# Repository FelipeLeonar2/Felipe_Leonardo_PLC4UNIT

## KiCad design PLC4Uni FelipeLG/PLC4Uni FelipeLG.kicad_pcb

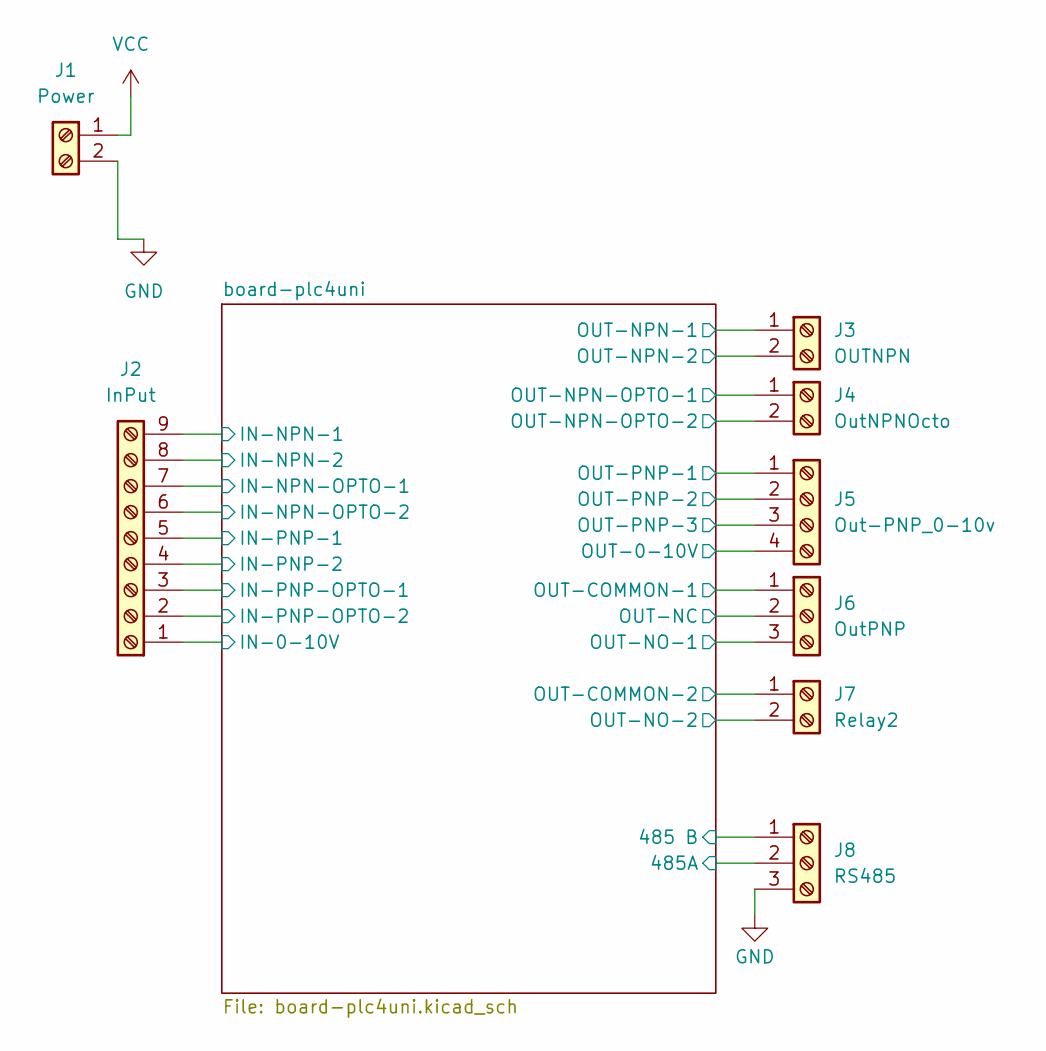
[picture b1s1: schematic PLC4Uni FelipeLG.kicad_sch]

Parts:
J1: Power; TerminalBlock_Phoenix_PT-1,5-2-5.0-H_1x02_P5.00mm_Horizontal
J2: InPut; TerminalBlock_Phoenix_PT-1,5-9-5.0-H_1x09_P5.00mm_Horizontal
J3: OUTNPN; TerminalBlock_Phoenix_PT-1,5-2-5.0-H_1x02_P5.00mm_Horizontal
J4: OutNPNOcto; TerminalBlock_Phoenix_PT-1,5-2-5.0-H_1x02_P5.00mm_Horizontal
J5: Out-PNP_0-10v; TerminalBlock_Phoenix_PT-1,5-4-5.0-H_1x04_P5.00mm_Horizontal
J6: OutPNP; TerminalBlock_Phoenix_PT-1,5-3-5.0-H_1x03_P5.00mm_Horizontal
J7: Relay2; TerminalBlock_Phoenix_PT-1,5-2-5.0-H_1x02_P5.00mm_Horizontal
J8: RS485; TerminalBlock_Phoenix_PT-1,5-3-5.0-H_1x03_P5.00mm_Horizontal

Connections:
/board-plc4uni/485 B: J8.1; also elsewhere on the board
/board-plc4uni/485A: J8.2; also elsewhere on the board
/board-plc4uni/IN-0-10V: J2.1; also elsewhere on the board
/board-plc4uni/IN-NPN-1: J2.9; also elsewhere on the board
/board-plc4uni/IN-NPN-2: J2.8; also elsewhere on the board
/board-plc4uni/IN-NPN-OPTO-1: J2.7; also elsewhere on the board
/board-plc4uni/IN-NPN-OPTO-2: J2.6; also elsewhere on the board
/board-plc4uni/IN-PNP-1: J2.5; also elsewhere on the board
/board-plc4uni/IN-PNP-2: J2.4; also elsewhere on the board
/board-plc4uni/IN-PNP-OPTO-1: J2.3; also elsewhere on the board
/board-plc4uni/IN-PNP-OPTO-2: J2.2; also elsewhere on the board
/board-plc4uni/OUT-0-10V: J5.4; also elsewhere on the board
/board-plc4uni/OUT-COMMON-1: J6.1; also elsewhere on the board
/board-plc4uni/OUT-COMMON-2: J7.1; also elsewhere on the board
/board-plc4uni/OUT-NC: J6.2; also elsewhere on the board
/board-plc4uni/OUT-NO-1: J6.3; also elsewhere on the board
/board-plc4uni/OUT-NO-2: J7.2; also elsewhere on the board
/board-plc4uni/OUT-NPN-1: J3.1; also elsewhere on the board
/board-plc4uni/OUT-NPN-2: J3.2; also elsewhere on the board
/board-plc4uni/OUT-NPN-OPTO-1: J4.1; also elsewhere on the board
/board-plc4uni/OUT-NPN-OPTO-2: J4.2; also elsewhere on the board
/board-plc4uni/OUT-PNP-1: J5.1; also elsewhere on the board
/board-plc4uni/OUT-PNP-2: J5.2; also elsewhere on the board
/board-plc4uni/OUT-PNP-3: J5.3; also elsewhere on the board
GND: J1.2, J8.3; also elsewhere on the board
VCC: J1.1; also elsewhere on the board

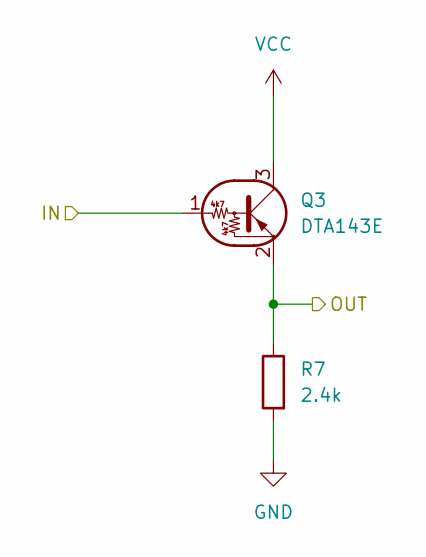
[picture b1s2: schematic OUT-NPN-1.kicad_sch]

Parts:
Q3: DTA143E; SC-59
R7: 2.4k; R_0603_1608Metric

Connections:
/board-plc4uni/OUT-NPN-2: Q3.2 (E), R7.2; also elsewhere on the board
/board-plc4uni/OUT-NPN-2/IN: Q3.1 (B); also elsewhere on the board
GND: R7.1; also elsewhere on the board
VCC: Q3.3 (C); also elsewhere on the board

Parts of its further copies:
Q7: DTA143E; SC-59
R21: 2.4k; R_0603_1608Metric

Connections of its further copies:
/board-plc4uni/OUT-NPN-1: Q7.2 (E), R21.2; also elsewhere on the board
/board-plc4uni/OUT-NPN-1/IN: Q7.1 (B); also elsewhere on the board
GND: R21.1; also elsewhere on the board
VCC: Q7.3 (C); also elsewhere on the board

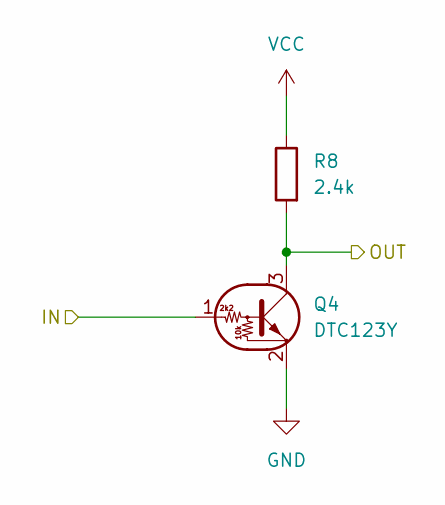
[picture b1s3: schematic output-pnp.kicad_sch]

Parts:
Q4: DTC123Y; SOT-23
R8: 2.4k; R_0603_1608Metric

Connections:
/board-plc4uni/OUT-PNP-1: Q4.3 (C), R8.1; also elsewhere on the board
/board-plc4uni/output-pnp-1/IN: Q4.1 (B); also elsewhere on the board
GND: Q4.2 (E); also elsewhere on the board
VCC: R8.2; also elsewhere on the board

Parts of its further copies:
Q8, Q9: DTC123Y; SOT-23
R22, R23: 2.4k; R_0603_1608Metric

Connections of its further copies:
/board-plc4uni/OUT-PNP-2: Q8.3 (C), R22.1; also elsewhere on the board
/board-plc4uni/OUT-PNP-3: Q9.3 (C), R23.1; also elsewhere on the board
/board-plc4uni/output-pnp-2/IN: Q8.1 (B); also elsewhere on the board
/board-plc4uni/output-pnp-3/IN: Q9.1 (B); also elsewhere on the board
GND: Q8.2 (E), Q9.2 (E); also elsewhere on the board
VCC: R22.2, R23.2; also elsewhere on the board

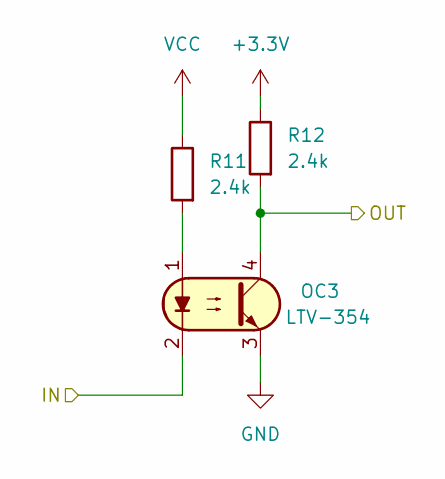
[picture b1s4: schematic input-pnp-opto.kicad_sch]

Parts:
OC3: FOD817S; SMDIP-4_W9.53mm; Part Number LTV-354
R11, R12: 2.4k; R_0603_1608Metric

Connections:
+3.3V: R12.2; also elsewhere on the board
/board-plc4uni/IN-PNP-OPTO-1: OC3.2; also elsewhere on the board
/board-plc4uni/input-pnp-opto-1/OUT: OC3.4, R12.1; also elsewhere on the board
GND: OC3.3; also elsewhere on the board
unnamed: OC3.1, R11.1
VCC: R11.2; also elsewhere on the board

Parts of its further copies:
OC5: FOD817S; SMDIP-4_W9.53mm; Part Number LTV-354
R16, R17: 2.4k; R_0603_1608Metric

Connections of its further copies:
+3.3V: R17.2; also elsewhere on the board
/board-plc4uni/IN-PNP-OPTO-2: OC5.2; also elsewhere on the board
/board-plc4uni/input-pnp-opto-2/OUT: OC5.4, R17.1; also elsewhere on the board
GND: OC5.3; also elsewhere on the board
unnamed: OC5.1, R16.1
VCC: R16.2; also elsewhere on the board

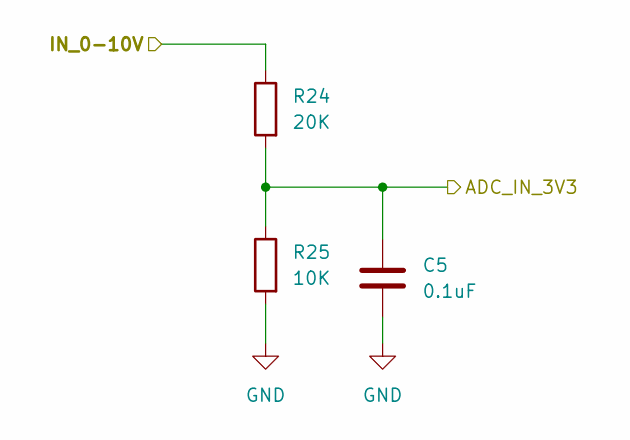
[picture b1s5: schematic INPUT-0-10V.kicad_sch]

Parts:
C5: 0.1uF; C_0201_0603Metric; LCSC C66501
R24: 20K; R_0603_1608Metric
R25: 10K; R_0603_1608Metric

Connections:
/board-plc4uni/IN-0-10V: R24.2; also elsewhere on the board
/board-plc4uni/INPUT-0-10V/ADC_IN_3V3: C5.2, R24.1, R25.2; also elsewhere on the board
GND: C5.1, R25.1; also elsewhere on the board

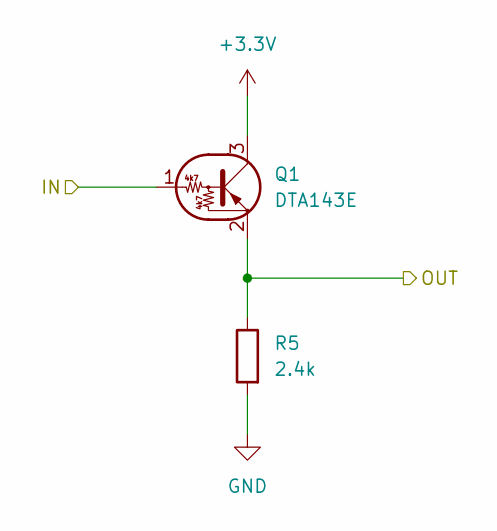
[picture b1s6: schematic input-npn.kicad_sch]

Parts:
Q1: DTA143E; SC-59
R5: 2.4k; R_0603_1608Metric

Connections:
+3.3V: Q1.3 (C); also elsewhere on the board
/board-plc4uni/IN-NPN-1: Q1.1 (B); also elsewhere on the board
/board-plc4uni/input-npn-1/OUT: Q1.2 (E), R5.2; also elsewhere on the board
GND: R5.1; also elsewhere on the board

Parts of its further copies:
Q5: DTA143E; SC-59
R15: 2.4k; R_0603_1608Metric

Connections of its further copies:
+3.3V: Q5.3 (C); also elsewhere on the board
/board-plc4uni/IN-NPN-2: Q5.1 (B); also elsewhere on the board
/board-plc4uni/input-npn-2/OUT: Q5.2 (E), R15.2; also elsewhere on the board
GND: R15.1; also elsewhere on the board

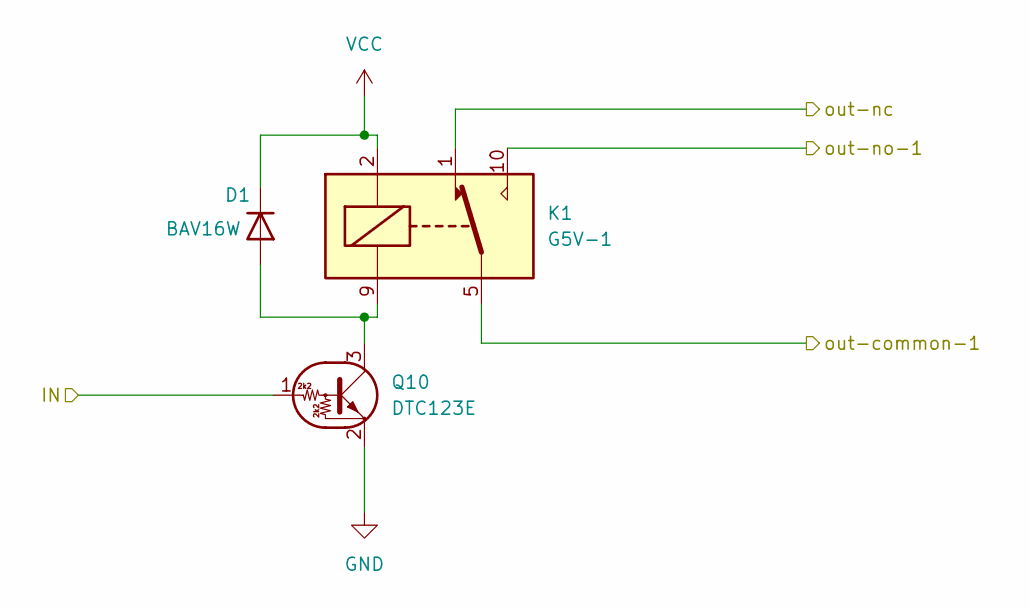
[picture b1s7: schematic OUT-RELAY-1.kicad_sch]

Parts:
D1: 1N4148WT; D_SOD-523; Part number BAV16W
K1: G5V-1; Relay_SPDT_Omron_G5V-1
Q10: DTC123E; SOT-23

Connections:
/board-plc4uni/OUT-COMMON-1: K1.5, K1.6; also elsewhere on the board
/board-plc4uni/OUT-NC: K1.1; also elsewhere on the board
/board-plc4uni/OUT-NO-1: K1.10; also elsewhere on the board
/board-plc4uni/OUT-RELAY-1/IN: Q10.1 (B); also elsewhere on the board
GND: Q10.2 (E); also elsewhere on the board
unnamed: D1.2 (A), K1.9, Q10.3 (C)
VCC: D1.1 (K), K1.2; also elsewhere on the board

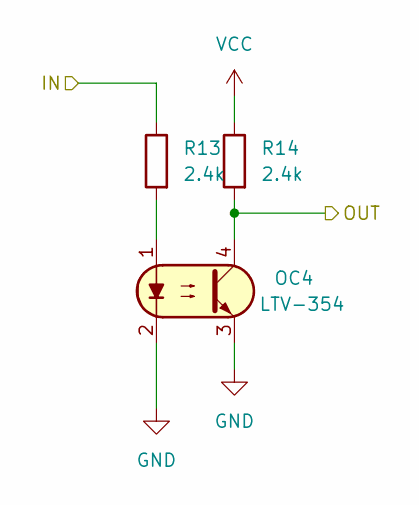
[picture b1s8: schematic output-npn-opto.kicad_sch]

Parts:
OC4: FOD817S; SMDIP-4_W9.53mm; Part Number LTV-354
R13, R14: 2.4k; R_0603_1608Metric

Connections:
/board-plc4uni/OUT-NPN-OPTO-1: OC4.4, R14.1; also elsewhere on the board
/board-plc4uni/output-npn-opto-1/IN: R13.2; also elsewhere on the board
GND: OC4.2, OC4.3; also elsewhere on the board
unnamed: OC4.1, R13.1
VCC: R14.2; also elsewhere on the board

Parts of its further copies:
OC6: FOD817S; SMDIP-4_W9.53mm; Part Number LTV-354
R19, R20: 2.4k; R_0603_1608Metric

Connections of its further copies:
/board-plc4uni/OUT-NPN-OPTO-2: OC6.4, R20.1; also elsewhere on the board
/board-plc4uni/output-npn-opto-2/IN: R19.2; also elsewhere on the board
GND: OC6.2, OC6.3; also elsewhere on the board
unnamed: OC6.1, R19.1
VCC: R20.2; also elsewhere on the board

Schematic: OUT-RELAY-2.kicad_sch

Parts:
D3: 1N4148WT; D_SOD-523; Part number BAV16W
K2: G5V-1; Relay_SPDT_Omron_G5V-1
Q11: DTC123E; SOT-23

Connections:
/board-plc4uni/OUT-COMMON-2: K2.5, K2.6; also elsewhere on the board
/board-plc4uni/OUT-NO-2: K2.10; also elsewhere on the board
/board-plc4uni/OUT-RELAY-2/IN: Q11.1 (B); also elsewhere on the board
GND: Q11.2 (E); also elsewhere on the board
unnamed: D3.2 (A), K2.9, Q11.3 (C)
VCC: D3.1 (K), K2.2; also elsewhere on the board

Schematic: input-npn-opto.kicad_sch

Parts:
OC1: FOD817S; SMDIP-4_W9.53mm; Part Number LTV-354
R3, R4: 2.4k; R_0603_1608Metric

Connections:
+3.3V: R4.2; also elsewhere on the board
/board-plc4uni/IN-NPN-OPTO-2: R3.1; also elsewhere on the board
/board-plc4uni/input-npn-opto-2/OUT: OC1.4, R4.1; also elsewhere on the board
GND: OC1.2, OC1.3; also elsewhere on the board
unnamed: OC1.1, R3.2

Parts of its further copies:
OC2: FOD817S; SMDIP-4_W9.53mm; Part Number LTV-354
R9, R10: 2.4k; R_0603_1608Metric

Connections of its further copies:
+3.3V: R10.2; also elsewhere on the board
/board-plc4uni/IN-NPN-OPTO-1: R9.1; also elsewhere on the board
/board-plc4uni/input-npn-opto-1/OUT: OC2.4, R10.1; also elsewhere on the board
GND: OC2.2, OC2.3; also elsewhere on the board
unnamed: OC2.1, R9.2

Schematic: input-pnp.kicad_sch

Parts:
Q2: DTC123E; SOT-23
R6: 2.4k; R_0603_1608Metric

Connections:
+3.3V: R6.2; also elsewhere on the board
/board-plc4uni/IN-PNP-1: Q2.1 (B); also elsewhere on the board
/board-plc4uni/input-pnp-1/OUT: Q2.3 (C), R6.1; also elsewhere on the board
GND: Q2.2 (E); also elsewhere on the board

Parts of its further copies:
Q6: DTC123E; SOT-23
R18: 2.4k; R_0603_1608Metric

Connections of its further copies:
+3.3V: R18.2; also elsewhere on the board
/board-plc4uni/IN-PNP-2: Q6.1 (B); also elsewhere on the board
/board-plc4uni/input-pnp-2/OUT: Q6.3 (C), R18.1; also elsewhere on the board
GND: Q6.2 (E); also elsewhere on the board

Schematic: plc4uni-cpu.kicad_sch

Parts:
C8: 1uF; C_0603_1608Metric; LCSC C89632
U2: ESP32-S3-WROOM-1

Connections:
+3.3V: C8.2, U2.2 (3V3), U2.3 (EN); also elsewhere on the board
/board-plc4uni/INPUT-0-10V/ADC_IN_3V3: U2.20 (IO12); also elsewhere on the board
/board-plc4uni/OUT-NPN-1/IN: U2.35 (IO42); also elsewhere on the board
/board-plc4uni/OUT-NPN-2/IN: U2.16 (IO46); also elsewhere on the board
/board-plc4uni/OUT-RELAY-1/IN: U2.15 (IO3); also elsewhere on the board
/board-plc4uni/OUT-RELAY-2/IN: U2.24 (IO47); also elsewhere on the board
/board-plc4uni/OUTPUT-0-10V/SCL: U2.27 (IO0); also elsewhere on the board
/board-plc4uni/OUTPUT-0-10V/SDA: U2.39 (IO1); also elsewhere on the board
/board-plc4uni/RS485/UART_RX: U2.36 (RXD0); also elsewhere on the board
/board-plc4uni/RS485/UART_TX: U2.37 (TXD0); also elsewhere on the board
/board-plc4uni/input-npn-1/OUT: U2.12 (IO8); also elsewhere on the board
/board-plc4uni/input-npn-2/OUT: U2.6 (IO6); also elsewhere on the board
/board-plc4uni/input-npn-opto-1/OUT: U2.5 (IO5); also elsewhere on the board
/board-plc4uni/input-npn-opto-2/OUT: U2.4 (IO4); also elsewhere on the board
/board-plc4uni/input-pnp-1/OUT: U2.10 (IO17); also elsewhere on the board
/board-plc4uni/input-pnp-2/OUT: U2.11 (IO18); also elsewhere on the board
/board-plc4uni/input-pnp-opto-1/OUT: U2.9 (IO16); also elsewhere on the board
/board-plc4uni/input-pnp-opto-2/OUT: U2.8 (IO15); also elsewhere on the board
/board-plc4uni/output-npn-opto-1/IN: U2.31 (IO38); also elsewhere on the board
/board-plc4uni/output-npn-opto-2/IN: U2.32 (IO39); also elsewhere on the board
/board-plc4uni/output-pnp-1/IN: U2.34 (IO41); also elsewhere on the board
/board-plc4uni/output-pnp-2/IN: U2.26 (IO45); also elsewhere on the board
/board-plc4uni/output-pnp-3/IN: U2.33 (IO40); also elsewhere on the board
GND: C8.1, U2.1 (GND), U2.40 (GND), U2.41 (GND); also elsewhere on the board

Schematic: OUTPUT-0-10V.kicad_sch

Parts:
C6: 1uF; C_0201_0603Metric; LCSC C1592
C7: 0.1uF; C_0201_0603Metric; LCSC C66501
D2: TVA; D_0201_0603Metric_TVS; LCSC C18199535
R26, R27: 4.7K; R_0603_1608Metric
U4: Sensirion_DFN-8-1EP_2.5x2.5mm_P0.5mm_EP1.1x1.7mm; LCSC C3152008

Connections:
+3.3V: R26.2, R27.2; also elsewhere on the board
/board-plc4uni/OUT-0-10V: C7.2, D2.1 (K), U4.6 (VOUT); also elsewhere on the board
/board-plc4uni/OUTPUT-0-10V/SCL: R26.1, U4.1 (SCLK); also elsewhere on the board
/board-plc4uni/OUTPUT-0-10V/SDA: R27.1, U4.2 (SDA); also elsewhere on the board
GND: C6.2, C7.1, D2.2 (A), U4.5 (GND), U4.9 (EP); also elsewhere on the board
unnamed: C6.1, U4.8 (V5V)
VCC: U4.4 (VCC); also elsewhere on the board

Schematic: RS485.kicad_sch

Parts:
R1, R2: 47K; R_0603_1608Metric
U1: TD321D485H-A-LB; TD321D48H-A

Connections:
+3.3V: U1.1 (VCC); also elsewhere on the board
/board-plc4uni/485 B: R2.2, U1.8 (B); also elsewhere on the board
/board-plc4uni/485A: R1.2, U1.9 (A); also elsewhere on the board
/board-plc4uni/RS485/UART_RX: U1.4 (RXD); also elsewhere on the board
/board-plc4uni/RS485/UART_TX: U1.3 (TXD); also elsewhere on the board
GND: U1.2 (GND); also elsewhere on the board
unnamed: R2.1, U1.10 (RGND)
unnamed: R1.1, U1.7 (VO)

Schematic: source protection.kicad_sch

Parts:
C1: 10uF; C_0603_1608Metric; LCSC C89632
C2: 100nF; C_0603_1608Metric; LCSC C519980
C3, C4: 22uF; C_1206_3216Metric; LCSC C7472972
F1: Fuse; Fuse_0603_1608Metric; Part number 1812L125/6V
L1: ANR4030T6R8M; L_APV_ANR4030; LCSC C77758
U3: AP63203WU; TSOT-23-6

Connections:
+3.3V: C3.1, C4.1, L1.2, U3.1 (FB); also elsewhere on the board
/board-plc4uni/source protection/INEN: F1.1, U3.2 (EN), U3.3 (IN)
/board-plc4uni/source protection/SW: C2.2, L1.1, U3.5 (SW)
GND: C1.2, C3.2, C4.2, U3.4 (GND); also elsewhere on the board
unnamed: C2.1, U3.6 (BST)
VCC: C1.1, F1.2; also elsewhere on the board

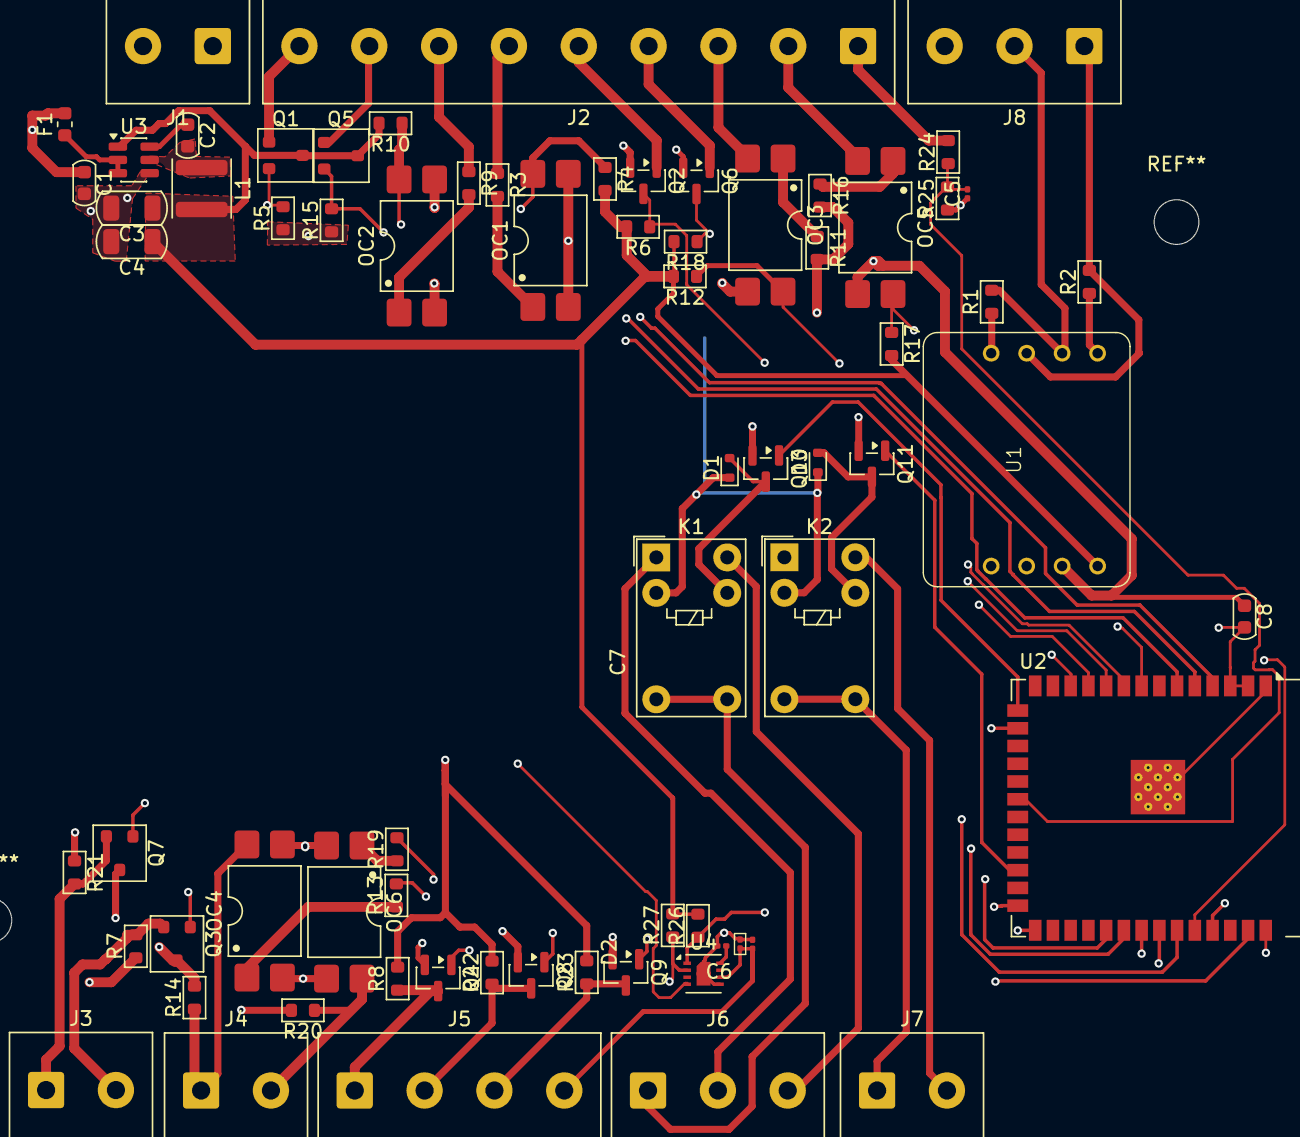
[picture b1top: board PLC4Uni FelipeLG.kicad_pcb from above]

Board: 4 copper layers, 71 parts (0 on the bottom side), 63 nets.

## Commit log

2025-10-06 Diseños 3D de la carcasa para el PLC
2025-10-09 Tarea 1
2025-10-09 Tarea 2
2025-10-10 Tarea 3 agregada
2025-11-20 Add files via upload
    Se agregaron los circuitos del PLC
2025-12-04 Add files via upload
    Updated Circuitos corregidos y pistas agregadas
